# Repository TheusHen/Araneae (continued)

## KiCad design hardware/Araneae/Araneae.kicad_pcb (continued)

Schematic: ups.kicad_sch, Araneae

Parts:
BT1, BT2: 1048; BAT_1048; PARTREV A
C1, C2, C3, C5, C6, C7, C12, C14, C18, C85, C86, C87: 100nF; C_0603_1608Metric
C4: 10nF; C_0603_1608Metric
C8, C16, C17: 10µF; C_0805_2012Metric
C9: 0.1µF; C_0603_1608Metric
C10: 4.7µF; C_0805_2012Metric
C11, C15: 1µF; C_0603_1608Metric
C13: 2.2µF; C_0603_1608Metric
D1: MBRS340; D_SMC
D2: LED; LED_0805_2012Metric
L1: 22µH; L_10.4x10.4_H4.8
Q1, Q3: PMOS; SOT-23
Q2, Q4: NMOS; SOT-23
R1, R16: 10mΩ; R_2512_6332Metric
R2, R3, R5, R11, R15, R17, R21, R23: 10k; R_0603_1608Metric
R4, R9, R10, R12, R14: 100k; R_0603_1608Metric
R6: 100Ω; R_0805_2012Metric
R7, R8: 4.7Ω; R_0603_1608Metric
R18: 301k; R_0603_1608Metric
R20: 124k; R_0603_1608Metric
R22: 95.3k; R_0603_1608Metric
R24: 30mΩ; R_2512_6332Metric
R120, R121: 4.7k; R_0603_1608Metric
TH1, TH2: 10k; R_0603_1608Metric
U1: LTC4412xS6; TSOT-23-6
U2: ISL94202IRTZ; QFN40P600X600X80-49N; PARTREV 3.00
U3, U4: IRLR7843; TO252
U5: LTC4015EUHF; QFN50P700X500X80-39N

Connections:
12V_SYSTEM: C85.1, U1.1 (VIN), U5.31 (SYS); also elsewhere on the board
19V: C17.1, Q3.3 (S), Q4.1 (D), R15.1, R16.1, R16.2, R20.2, U5.32 (CLN), U5.33 (CLP), U5.35 (VIN); also elsewhere on the board
+3V3: C6.2, R5.2, R17.2, U1.3 (CTL); also elsewhere on the board
+12V: D1.1 (K), Q1.1 (D), Q1.3 (S), R1.1, U1.6 (SENSE), U2.1 (VC8), U2.3 (VC7), U2.5 (VC6), U2.7 (VC5), U2.9 (VC4), U2.47 (CSI1), U2.48 (VBATT); also elsewhere on the board
/UPS Subsystem/2P5VCC: C11.1, C13.1, U5.22 (2P5VCC)
/UPS Subsystem/+12V_BAT: BT2.P2, D1.2 (A), R1.2, U2.10 (CB4), U2.46 (CSI2)
/UPS Subsystem/BAT_P: R24.2, U5.18 (BATSENS), U5.19 (CSN)
/UPS Subsystem/BG: Q2.2 (G), U5.26 (BG)
/UPS Subsystem/CCREFM: C7.2, R18.1, U5.16 (CCREFM)
/UPS Subsystem/CCREFP: C7.1, R18.2, U5.17 (CCREFP)
/UPS Subsystem/CSP: C86.2, L1.1, R24.1, U5.20 (CSP)
/UPS Subsystem/DVCC: C8.1, C10.1, C16.1, U5.3 (DVCC), U5.4 (SCL), U5.5 (SDA), U5.28 (INTVCC), U5.36 (CHEM0)
/UPS Subsystem/SW: C12.2, L1.2, Q2.1 (D), Q4.3 (S), U5.23 (SW)
/UPS Subsystem/TG: Q4.2 (G), U5.24 (TG)
/UPS Subsystem/UPS1_N1: BT1.N1, BT1.P2, U2.14 (CB2)
/UPS Subsystem/UPS1_N2: BT1.N2, BT1.P1, U2.15 (VC1), U2.16 (CB1)
/UPS Subsystem/UPS2_N2: BT2.N2, BT2.P1, U2.11 (VC3), U2.12 (CB3), U2.13 (VC2)
EXT_I2C_SCL: R120.2, U2.25 (SCL); also elsewhere on the board
EXT_I2C_SDA: R121.2, U2.26 (SDAI), U2.27 (SDAO); also elsewhere on the board
GND: BT2.N1, C1.2, C2.1, C3.2, C4.2, C5.1, C9.2, C10.2, C11.2, C13.2, C14.2, C15.2, C16.2, C18.2, C87.2, Q2.3 (S), R2.2, R3.2, R4.1, R8.1, R9.2, R15.2, R22.2, TH2.2, U1.2 (GND), U2.17 (VC0), U2.18 (VSS), U2.24 (ADDR), U2.28 (VSS), U2.29 (VSS), U2.44 (PCFET), U2.49 (VSS), U3.2, U4.2, U5.1 (CELLS1), U5.2 (CELLS2), U5.7 (SGND), U5.13 (EQ), U5.14 (GND), U5.21 (MPPT), U5.37 (CHEM1), U5.39 (EXP); also elsewhere on the board
LTC4015_ALERT: R17.1, U5.6 (~SMBALERT); also elsewhere on the board
unnamed: C8.2, C9.1
unnamed: C14.1, R23.1
unnamed: C17.2, C18.1
unnamed: D2.2 (A), U1.4 (STAT)
unnamed: D2.1 (K), R5.1
unnamed: Q1.2 (G), U1.5 (GATE)
unnamed: Q3.1 (D), U5.34 (INFET)
unnamed: Q3.2 (G), U5.29 (OUTFET)
unnamed: R6.2, R8.2, U4.1
unnamed: R7.1, U3.1
unnamed: C1.1, U2.41 (C1)
unnamed: C2.2, U2.40 (C2)
unnamed: C3.1, U2.39 (C3)
unnamed: R6.1, U2.45 (CFET)
unnamed: R2.1, U2.37 (CHMON)
unnamed: R7.2, U2.42 (DFET)
unnamed: R4.2, U2.33 (FETSOFF)
unnamed: R3.1, U2.38 (LDMON)
unnamed: R14.2, U2.32 (PSD)
unnamed 243: C87.1, R10.1, R11.1, R12.1, R14.1, R120.1, R121.1, U2.36 (RGO); also elsewhere on the board
unnamed: C4.1, R9.1, U2.22 (TEMPO)
unnamed: C6.1, U2.43 (VDD)
unnamed: C5.2, U2.19 (VREF)
unnamed: TH1.2, U2.20 (XT1)
unnamed: TH1.1, U2.21 (XT2)
unnamed: R10.2, U2.35 (~EOC)
unnamed: R11.2, U2.31 (~INT)
unnamed: R12.2, U2.34 (~SD)
unnamed: U3.3, U4.3
unnamed: C12.1, U5.25 (BOOST)
unnamed: C86.1, U5.15 (CSPM5)
unnamed: C15.1, U5.27 (DRVCC)
unnamed: R21.1, TH2.1, U5.11 (NTC)
unnamed: R21.2, U5.12 (NTCBIAS)
unnamed: R22.1, U5.10 (RT)
unnamed: C85.2, U5.30 (SYSM5)
unnamed: R20.1, U5.8 (UVCLFB)
unnamed: R23.2, U5.9 (VC)

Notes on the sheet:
Official Quality Certified LFP 26650 3.2v 2500Mh Grade A_P LiFePO4 Battery Rechargeable Battery Golfcarts RV Deep Cycle Battery
1.2 × (124k + 10k) / 10k ≈ 16.1V
3.2v x 4 = 12,8v

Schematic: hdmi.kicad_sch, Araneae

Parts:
F1: 500mA; Fuse_1206_3216Metric
J3: HDMI_A; HDMI_A_Molex_208658-1001_Horizontal

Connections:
+5V: F1.2; also elsewhere on the board
/CM4/HDMI0_CEC: J3.13 (CEC); also elsewhere on the board
/CM4/HDMI0_CLK_N: J3.12 (CK_N); also elsewhere on the board
/CM4/HDMI0_CLK_P: J3.10 (CK_P); also elsewhere on the board
/CM4/HDMI0_HPD: J3.19 (HPD); also elsewhere on the board
/CM4/HDMI0_SCL: J3.15 (SCL); also elsewhere on the board
/CM4/HDMI0_SDA: J3.16 (SDA); also elsewhere on the board
/CM4/HDMI0_TX0_N: J3.9 (D0_N); also elsewhere on the board
/CM4/HDMI0_TX0_P: J3.7 (D0_P); also elsewhere on the board
/CM4/HDMI0_TX1_N: J3.6 (D1_N); also elsewhere on the board
/CM4/HDMI0_TX1_P: J3.4 (D1_P); also elsewhere on the board
/CM4/HDMI0_TX2_N: J3.3 (D2_N); also elsewhere on the board
/CM4/HDMI0_TX2_P: J3.1 (D2_P); also elsewhere on the board
GND: J3.2 (D2S), J3.5 (D1S), J3.8 (D0S), J3.11 (CKS), J3.17 (GND), J3.SH; also elsewhere on the board
unnamed: F1.1, J3.18 (+5V)

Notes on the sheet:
CM4 Datasheet doesn't needs TVS for HDMI

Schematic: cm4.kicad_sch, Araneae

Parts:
R25: 220Ω; R_0805_2012Metric
X1, X2: DF40HC_3.0_-100DS-0.4V_58; HRS_DF40HC_3.0_-100DS-0.4V_58

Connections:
+1V8: X1.88, X1.90, X1.94, X1.96; also elsewhere on the board
+3V3: X1.78, X1.84, X1.86; also elsewhere on the board
+5V: X1.77, X1.79, X1.81, X1.83, X1.85, X1.87; also elsewhere on the board
/CM4/CD1_SCL: X1.80; also elsewhere on the board
/CM4/CD1_SDA: X1.82; also elsewhere on the board
/CM4/CM4_USB_D_N: X2.3; also elsewhere on the board
/CM4/CM4_USB_D_P: X2.5; also elsewhere on the board
/CM4/DSI1_CLK_N: X2.87; also elsewhere on the board
/CM4/DSI1_CLK_P: X2.89; also elsewhere on the board
/CM4/DSI1_D0_N: X2.75; also elsewhere on the board
/CM4/DSI1_D0_P: X2.77; also elsewhere on the board
/CM4/DSI1_D1_N: X2.81; also elsewhere on the board
/CM4/DSI1_D1_P: X2.83; also elsewhere on the board
/CM4/DSI1_D2_N: X2.93; also elsewhere on the board
/CM4/DSI1_D2_P: X2.95; also elsewhere on the board
/CM4/DSI1_D3_N: X2.94; also elsewhere on the board
/CM4/DSI1_D3_P: X2.96; also elsewhere on the board
/CM4/ETH1_LED1: X1.15; also elsewhere on the board
/CM4/ETH1_LED2: X1.17; also elsewhere on the board
/CM4/ETH1_MX1_N: X1.10; also elsewhere on the board
/CM4/ETH1_MX1_P: X1.12; also elsewhere on the board
/CM4/ETH1_MX2_N: X1.6; also elsewhere on the board
/CM4/ETH1_MX2_P: X1.4; also elsewhere on the board
/CM4/ETH1_MX3_N: X1.9; also elsewhere on the board
/CM4/ETH1_MX3_P: X1.11; also elsewhere on the board
/CM4/ETH1_MX4_N: X1.5; also elsewhere on the board
/CM4/ETH1_MX4_P: X1.3; also elsewhere on the board
/CM4/ETH_INTRP_N: X1.41; also elsewhere on the board
/CM4/ETH_SCS_N: X1.45; also elsewhere on the board
/CM4/HDMI0_CEC: X2.51; also elsewhere on the board
/CM4/HDMI0_CLK_N: X2.90; also elsewhere on the board
/CM4/HDMI0_CLK_P: X2.88; also elsewhere on the board
/CM4/HDMI0_HPD: X2.53; also elsewhere on the board
/CM4/HDMI0_SCL: X2.100; also elsewhere on the board
/CM4/HDMI0_SDA: X2.99; also elsewhere on the board
/CM4/HDMI0_TX0_N: X2.84; also elsewhere on the board
/CM4/HDMI0_TX0_P: X2.82; also elsewhere on the board
/CM4/HDMI0_TX1_N: X2.78; also elsewhere on the board
/CM4/HDMI0_TX1_P: X2.76; also elsewhere on the board
/CM4/HDMI0_TX2_N: X2.72; also elsewhere on the board
/CM4/HDMI0_TX2_P: X2.70; also elsewhere on the board
/CM4/SD_CLK: X1.57; also elsewhere on the board
/CM4/SD_DAT0: X1.63; also elsewhere on the board
/CM4/SD_DAT1: X1.67; also elsewhere on the board
/CM4/SD_DAT2: X1.69; also elsewhere on the board
/CM4/SD_DAT3: X1.61; also elsewhere on the board
/CM4/SD_PWR: X1.62; also elsewhere on the board
/CM4/SD_PWR_ON: X1.75; also elsewhere on the board
/CM4/SSD_3V3_EN: X2.11
/CM4/SSD_CLKREQ_IN: X2.2
/CM4/SSD_PERST_IN: X2.9
/CM4/SSD_PERn0: X2.18; also elsewhere on the board
/CM4/SSD_PERp0: X2.16; also elsewhere on the board
/CM4/SSD_PETn0: X2.24; also elsewhere on the board
/CM4/SSD_PETp0: X2.22; also elsewhere on the board
/CM4/SSD_REFCLKn: X2.12; also elsewhere on the board
/CM4/SSD_REFCLKp: X2.10; also elsewhere on the board
/CM4/USB_HUB_RESET_N: X1.100; also elsewhere on the board
/CM4/WATCHDOG_WDI: X1.46; also elsewhere on the board
Bottom_Fan_PWM: X1.28; also elsewhere on the board
Bottom_Fan_Sense: X1.50; also elsewhere on the board
EXT_GPIO1: X1.27; also elsewhere on the board
EXT_GPIO2: X1.25; also elsewhere on the board
EXT_GPIO3: X1.24; also elsewhere on the board
EXT_GPIO4: X1.30; also elsewhere on the board
EXT_GPIO5: X1.48; also elsewhere on the board
EXT_GPIO6: X2.19; also elsewhere on the board
EXT_GPIO7: X2.31; also elsewhere on the board
EXT_GPIO8: X2.25; also elsewhere on the board
EXT_GPIO9: X2.23; also elsewhere on the board
EXT_GPIO10: X2.37; also elsewhere on the board
EXT_I2C_SCL: X1.56; also elsewhere on the board
EXT_I2C_SDA: X1.58; also elsewhere on the board
EXT_PWM0: X1.49; also elsewhere on the board
EXT_PWM1: X1.26; also elsewhere on the board
EXT_SPI_CS0: X1.39; also elsewhere on the board
EXT_SPI_CS1: X1.37; also elsewhere on the board
EXT_SPI_MISO: X1.40; also elsewhere on the board
EXT_SPI_MOSI: X1.44; also elsewhere on the board
EXT_SPI_SCLK: X1.38; also elsewhere on the board
EXT_UART_RX: X1.34; also elsewhere on the board
EXT_UART_TX: X1.54; also elsewhere on the board
GND: X1.1, X1.2, X1.7, X1.8, X1.13, X1.14, X1.22, X1.23, X1.32, X1.33, X1.42, X1.43, X1.52, X1.53, X1.59, X1.60, X1.65, X1.66, X1.71, X1.74, X1.98, X2.1, X2.7, X2.8, X2.13, X2.14, X2.20, X2.26, X2.32, X2.38, X2.44, X2.50, X2.55, X2.56, X2.61, X2.62, X2.67, X2.68, X2.73, X2.74, X2.79, X2.80, X2.85, X2.86, X2.91, X2.92, X2.97, X2.98; also elsewhere on the board
LTC4015_ALERT: X1.47; also elsewhere on the board
unnamed: R25.1, X1.92
RESET_GLOBAL: R25.2; also elsewhere on the board
RX_DEBUG: X1.51; also elsewhere on the board
SCL_DEBUG: X1.35; also elsewhere on the board
SDA_DEBUG: X1.36; also elsewhere on the board
TX_DEBUG: X1.55; also elsewhere on the board
Top_Fan_PWM: X1.31; also elsewhere on the board
Top_Fan_Sense: X1.29; also elsewhere on the board

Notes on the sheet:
CM4 Lite w/ WiFi

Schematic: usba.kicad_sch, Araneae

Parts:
C30, C31: 100nF; C_0603_1608Metric
D8, D9, D10, D11, D12, D13: ESD_USB; D_SOD-323
J4: USB_A_Stacked; USB_A_CUI_UJ2-ADH-TH_Horizontal_Stacked
J5: USB_A; USB_A_Wuerth_614004134726_Horizontal
R37, R38: 1MΩ; R_0603_1608Metric
U8, U9, U10: TPS2041B; SOT-23-5

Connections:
+5V: U8.5 (IN), U9.5 (IN), U10.5 (IN); also elsewhere on the board
/USB Hub/USBA1_D_N: D9.2 (A2), J4.2 (D1_N); also elsewhere on the board
/USB Hub/USBA1_D_P: D8.2 (A2), J4.3 (D1_P); also elsewhere on the board
/USB Hub/USBA1_FAULT_N: U10.3 (~OC); also elsewhere on the board
/USB Hub/USBA1_PWR_EN: U10.4 (~EN); also elsewhere on the board
/USB Hub/USBA2_D_N: D10.2 (A2), J4.7 (D2_P); also elsewhere on the board
/USB Hub/USBA2_D_P: D11.2 (A2), J4.6 (D2_N); also elsewhere on the board
/USB Hub/USBA2_FAULT_N: U8.3 (~OC); also elsewhere on the board
/USB Hub/USBA2_PWR_EN: U8.4 (~EN); also elsewhere on the board
/USB Hub/USBA3_D_N: D12.2 (A2), J5.2 (D_N); also elsewhere on the board
/USB Hub/USBA3_D_P: D13.2 (A2), J5.3 (D_P); also elsewhere on the board
/USB Hub/USBA3_FAULT_N: U9.3 (~OC); also elsewhere on the board
/USB Hub/USBA3_PWR_EN: U9.4 (~EN); also elsewhere on the board
GND: C30.2, C31.2, D8.1 (A1), D9.1 (A1), D10.1 (A1), D11.1 (A1), D12.1 (A1), D13.1 (A1), J4.4 (GND1), J4.8 (GND2), J5.4 (GND), U8.2 (GND), U9.2 (GND), U10.2 (GND); also elsewhere on the board
unnamed: C30.1, R37.1
unnamed: C31.1, R38.2
unnamed: J4.9 (Shield), R37.2
unnamed: J4.1 (VBUS1), U9.1 (OUT)
unnamed: J4.5 (VBUS2), U8.1 (OUT)
unnamed: J5.5 (Shield), R38.1
unnamed: J5.1 (VBUS), U10.1 (OUT)

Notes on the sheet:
USB ports operate at USB 2.0 speeds due to CM4 limitations. High-speed storage is provided via PCIe.

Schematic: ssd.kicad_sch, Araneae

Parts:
C19: 100nF; C_0603_1608Metric
D3: LED; LED_0805_2012Metric
J1: MDT320M01001; AMPHENOL_MDT320M01001; PARTREV 7
R26: 1k; R_0603_1608Metric
R27: 10k; R_0603_1608Metric
R28: 100k; R_0603_1608Metric
R29: 33R; R_0603_1608Metric
Y1: 32.768kHz; Oscillator_SMD_Abracon_ASCO-4Pin_1.6x1.2mm

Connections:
3V3_SSD: C19.1, J1.2, J1.4, J1.12, J1.14, J1.16, J1.18, J1.70, J1.72, J1.74, R26.1, R27.2, R28.2, Y1.4 (VDD); also elsewhere on the board
/CM4/SSD_PERn0: J1.47; also elsewhere on the board
/CM4/SSD_PERp0: J1.49; also elsewhere on the board
/CM4/SSD_PETn0: J1.41; also elsewhere on the board
/CM4/SSD_PETp0: J1.43; also elsewhere on the board
/CM4/SSD_PEWAKE#: J1.54, R27.1
/CM4/SSD_REFCLKn: J1.53; also elsewhere on the board
/CM4/SSD_REFCLKp: J1.55; also elsewhere on the board
/CM4/SSD_SUSCLK: J1.68, R29.2
/SSD PCle/SSD_CLKREQ#: J1.52; also elsewhere on the board
/SSD PCle/SSD_PERST#: J1.50; also elsewhere on the board
GND: C19.2, J1.1, J1.3, J1.9, J1.15, J1.21, J1.27, J1.33, J1.39, J1.45, J1.51, J1.57, J1.71, J1.73, J1.75, Y1.2 (GND); also elsewhere on the board
unnamed: D3.2 (A), R26.2
unnamed: D3.1 (K), J1.10
unnamed: R29.1, Y1.3 (OUT)
unnamed: R28.1, Y1.1 (Tri-State)

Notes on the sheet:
SSD PCIe

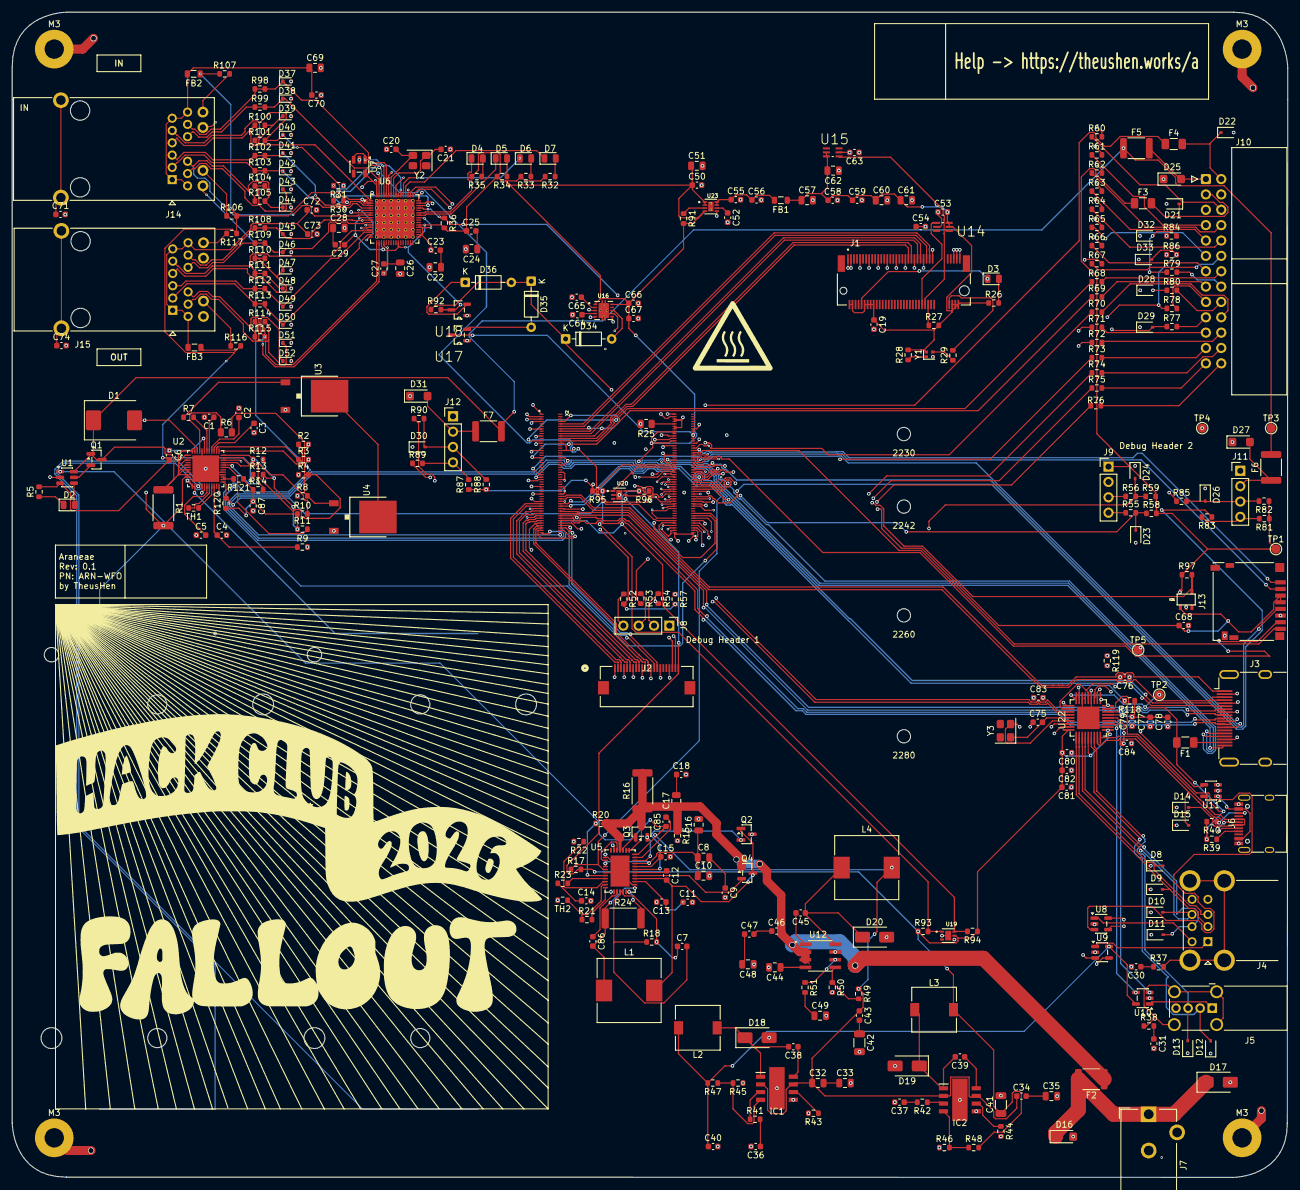
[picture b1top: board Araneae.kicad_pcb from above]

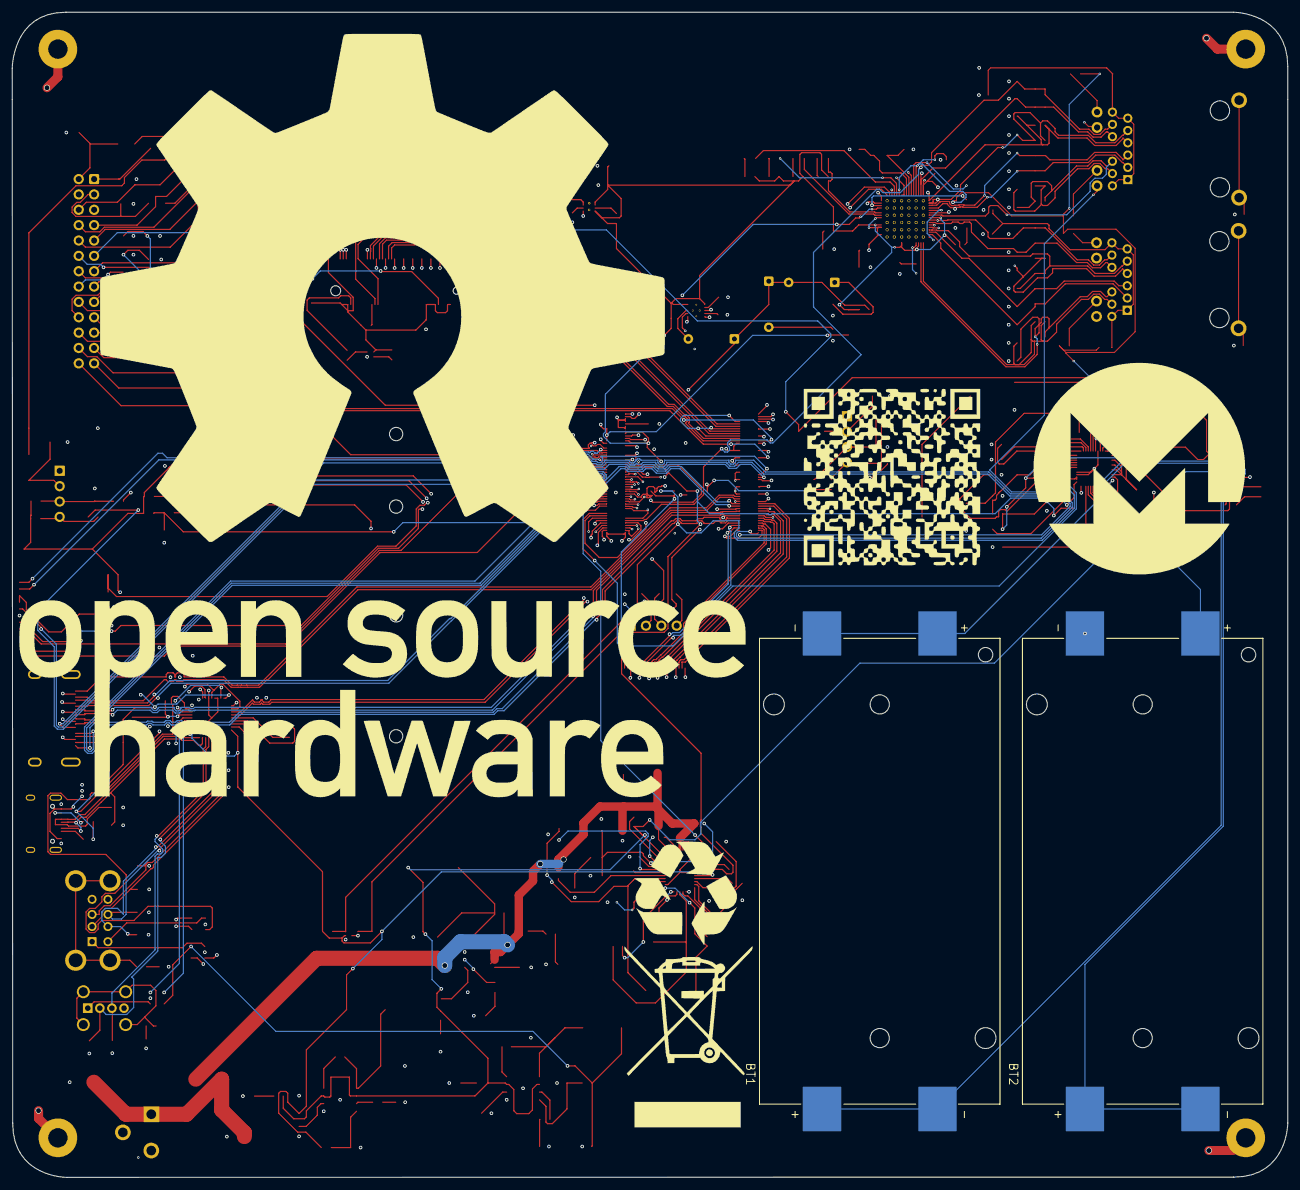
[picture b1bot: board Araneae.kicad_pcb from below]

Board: 6 copper layers, 211.0 x 192.7 mm, 338 parts (2 on the bottom side), 284 nets.

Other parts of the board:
2230, 2242, 2260, 2280: MountingHole_2.2mm_M2
M3, M3#2, M3#3, M3#4: MountingHole_3.2mm_M3_Pad
R13: 10k; R_0603_1608Metric

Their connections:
+3V3: R13.1; also elsewhere on the board
GND: M3.1, M3#2.1, M3#3.1, M3#4.1; also elsewhere on the board
unnamed 243: R13.2; also elsewhere on the board

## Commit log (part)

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2026-03-10 We Stand with Public Domain!
2026-03-31 Modify CodeQL workflow for branch and language support
    Updated CodeQL workflow to support multiple branches and languages.
2026-03-31 Configure Dependabot for multiple package ecosystems
    Added configurations for GitHub Actions, Cargo, and Docker package ecosystems with specific schedules and labels.
2026-03-31 Add SBOM and Scorecard workflows; include README and logo assets
2026-03-31 Refactor workflow YAML files for SBOM and Scorecard: improve formatting and readability
2026-03-31 Update Scorecard workflow: upgrade action version and add artifact upload steps
2026-03-31 Ajusted logo for Dark and White mode on GitHub
2026-04-01 Add CODEOWNERS file to define repository ownership
2026-04-06 chore(deps): bump github/codeql-action from 3 to 4
    Bumps [github/codeql-action](https://github.com/github/codeql-action) from 3 to 4.
    - [Release notes](https://github.com/github/codeql-action/releases)
    - [Changelog](https://github.com/github/codeql-action/blob/main/CHANGELOG.md)
    - [Commits](https://github.com/github/codeql-action/compare/v3...v4)
    ---
    updated-dependencies:
2026-04-06 chore(deps): bump actions/upload-artifact from 4.6.1 to 7.0.0
    Bumps [actions/upload-artifact](https://github.com/actions/upload-artifact) from 4.6.1 to 7.0.0.
    - [Release notes](https://github.com/actions/upload-artifact/releases)
    - [Commits](https://github.com/actions/upload-artifact/compare/4cec3d8aa04e39d1a68397de0c4cd6fb9dce8ec1...bbbca2ddaa5d8feaa63e36b76fdaad77386f024f)
    ---
    updated-dependencies:
    - dependency-name: actions/upload-artifact
2026-04-06 chore(deps): bump ossf/scorecard-action from 2.4.1 to 2.4.3
    Bumps [ossf/scorecard-action](https://github.com/ossf/scorecard-action) from 2.4.1 to 2.4.3.
    - [Release notes](https://github.com/ossf/scorecard-action/releases)
    - [Changelog](https://github.com/ossf/scorecard-action/blob/main/RELEASE.md)
    - [Commits](https://github.com/ossf/scorecard-action/compare/f49aabe0b5af0936a0987cfb85d86b75731b0186...4eaacf0543bb3f2c246792bd56e8cdeffafb205a)
    ---
    updated-dependencies:
2026-04-11 docs: add security policy, contributing guide, code of conduct, and funding config
2026-04-12 chore(hardware): add KiCad project, Git LFS for CAD outputs, extend gitignore
2026-04-13 chore: update security policy and enhance CodeQL workflows
    - Added preferred private reporting channels for security vulnerabilities in SECURITY.md.
    - Enhanced CodeQL workflows to detect supported languages and skip analysis if none are found.
    - Updated permissions and checkout actions in various workflows for consistency.
    - Added SBOM generation and upload steps in sbom.yml.
2026-04-13 chore(deps): bump actions/checkout from 4 to 6
    Bumps [actions/checkout](https://github.com/actions/checkout) from 4 to 6.
    - [Release notes](https://github.com/actions/checkout/releases)
    - [Changelog](https://github.com/actions/checkout/blob/main/CHANGELOG.md)
    - [Commits](https://github.com/actions/checkout/compare/v4...v6)
    ---
    updated-dependencies:
2026-04-13 chore(deps): bump github/codeql-action
    Bumps [github/codeql-action](https://github.com/github/codeql-action) from d4b3ca9fa7f69d38bfcd667bdc45bc373d16277e to c10b8064de6f491fea524254123dbe5e09572f13.
    - [Release notes](https://github.com/github/codeql-action/releases)
    - [Changelog](https://github.com/github/codeql-action/blob/main/CHANGELOG.md)
    - [Commits](https://github.com/github/codeql-action/compare/d4b3ca9fa7f69d38bfcd667bdc45bc373d16277e...c10b8064de6f491fea524254123dbe5e09572f13)
    ---
    updated-dependencies:
2026-04-22 Update GitHub Actions workflow for Scorecard analysis
2026-04-22 chore(deps): bump actions/checkout from 4.3.1 to 6.0.2
    Bumps [actions/checkout](https://github.com/actions/checkout) from 4.3.1 to 6.0.2.
    - [Release notes](https://github.com/actions/checkout/releases)
    - [Changelog](https://github.com/actions/checkout/blob/main/CHANGELOG.md)
    - [Commits](https://github.com/actions/checkout/compare/34e114876b0b11c390a56381ad16ebd13914f8d5...de0fac2e4500dabe0009e67214ff5f5447ce83dd)
    ---
    updated-dependencies:
2026-04-22 chore(deps): bump actions/upload-artifact from 4.6.2 to 7.0.1
    Bumps [actions/upload-artifact](https://github.com/actions/upload-artifact) from 4.6.2 to 7.0.1.
    - [Release notes](https://github.com/actions/upload-artifact/releases)
    - [Commits](https://github.com/actions/upload-artifact/compare/v4.6.2...043fb46d1a93c77aae656e7c1c64a875d1fc6a0a)
    ---
    updated-dependencies:
    - dependency-name: actions/upload-artifact
2026-04-27 chore(deps): bump actions/upload-artifact from 4 to 7
    Bumps [actions/upload-artifact](https://github.com/actions/upload-artifact) from 4 to 7.
    - [Release notes](https://github.com/actions/upload-artifact/releases)
    - [Commits](https://github.com/actions/upload-artifact/compare/v4...v7)
    ---
    updated-dependencies:
    - dependency-name: actions/upload-artifact
2026-05-09 Add CI workflow for PCB checks and artifact generation
    - Created a GitHub Actions workflow (`ci.yml`) to automate hardware checks including ERC, DRC, and plot generation for KiCad projects.
    - Added a new footprint for the SON50P200X200X80-9N component in `SON50P200X200X80-9N.kicad_mod`.
    - Introduced a new symbol for the TPS22965DSGR component in `TPS22965DSGR.kicad_sym`.
    - Added a configuration file `kibot.yaml` for generating fabrication files and other outputs.
2026-05-09 refactor: update CI workflow for KiCad checks and improve README formatting
2026-05-09 feat: add PCB_SVG_LAYERS environment variable and update SVG export command
2026-05-09 fix: rename PCB_SVG_LAYERS to PCB_PLOT_LAYERS and update export commands for KiCad
2026-05-09 refactor: remove unused output configurations from kibot.yaml
2026-05-09 feat: update fabrication file generation to use KiCad CLI and add support for gerbers, drill files, and BOM export
2026-05-18 Add Araneae OS OpenWrt starter kit
    Introduce an OpenWrt Image Builder scaffold for the Raspberry Pi CM4/RPi4 target, including package lists, first-boot provisioning, WireGuard, storage, Docker, and Mattermost defaults.
    Add documentation and release automation so Araneae OS images can be built reproducibly from changes under araneae-os/.
2026-05-18 Fix Araneae OS image rootfs sizing
    Pass ROOTFS_PARTSIZE from the OpenWrt profile so the Raspberry Pi image has enough space for LuCI, Docker, storage packages, and Mattermost support.
    Enable verbose Image Builder logs through the profile to make future CI failures easier to diagnose.
2026-05-18 Fix OpenWrt package selection
    Replace unavailable WireGuard LuCI package with luci-proto-wireguard and drop packages that are not present for OpenWrt 24.10.6 on bcm27xx/bcm2711.
    Remove the default dnsmasq package when installing dnsmasq-full to avoid Image Builder file clashes.
2026-05-18 Fix Araneae OS artifact collection
    Collect built images from araneae-os/dist, preferring the ext4 factory image for the release artifact, and include generated metadata files.
2026-06-22 chore(deps): bump actions/checkout from 4 to 7
    Bumps [actions/checkout](https://github.com/actions/checkout) from 4 to 7.
    - [Release notes](https://github.com/actions/checkout/releases)
    - [Commits](https://github.com/actions/checkout/compare/v4...v7)
    ---
    updated-dependencies:
    - dependency-name: actions/checkout
